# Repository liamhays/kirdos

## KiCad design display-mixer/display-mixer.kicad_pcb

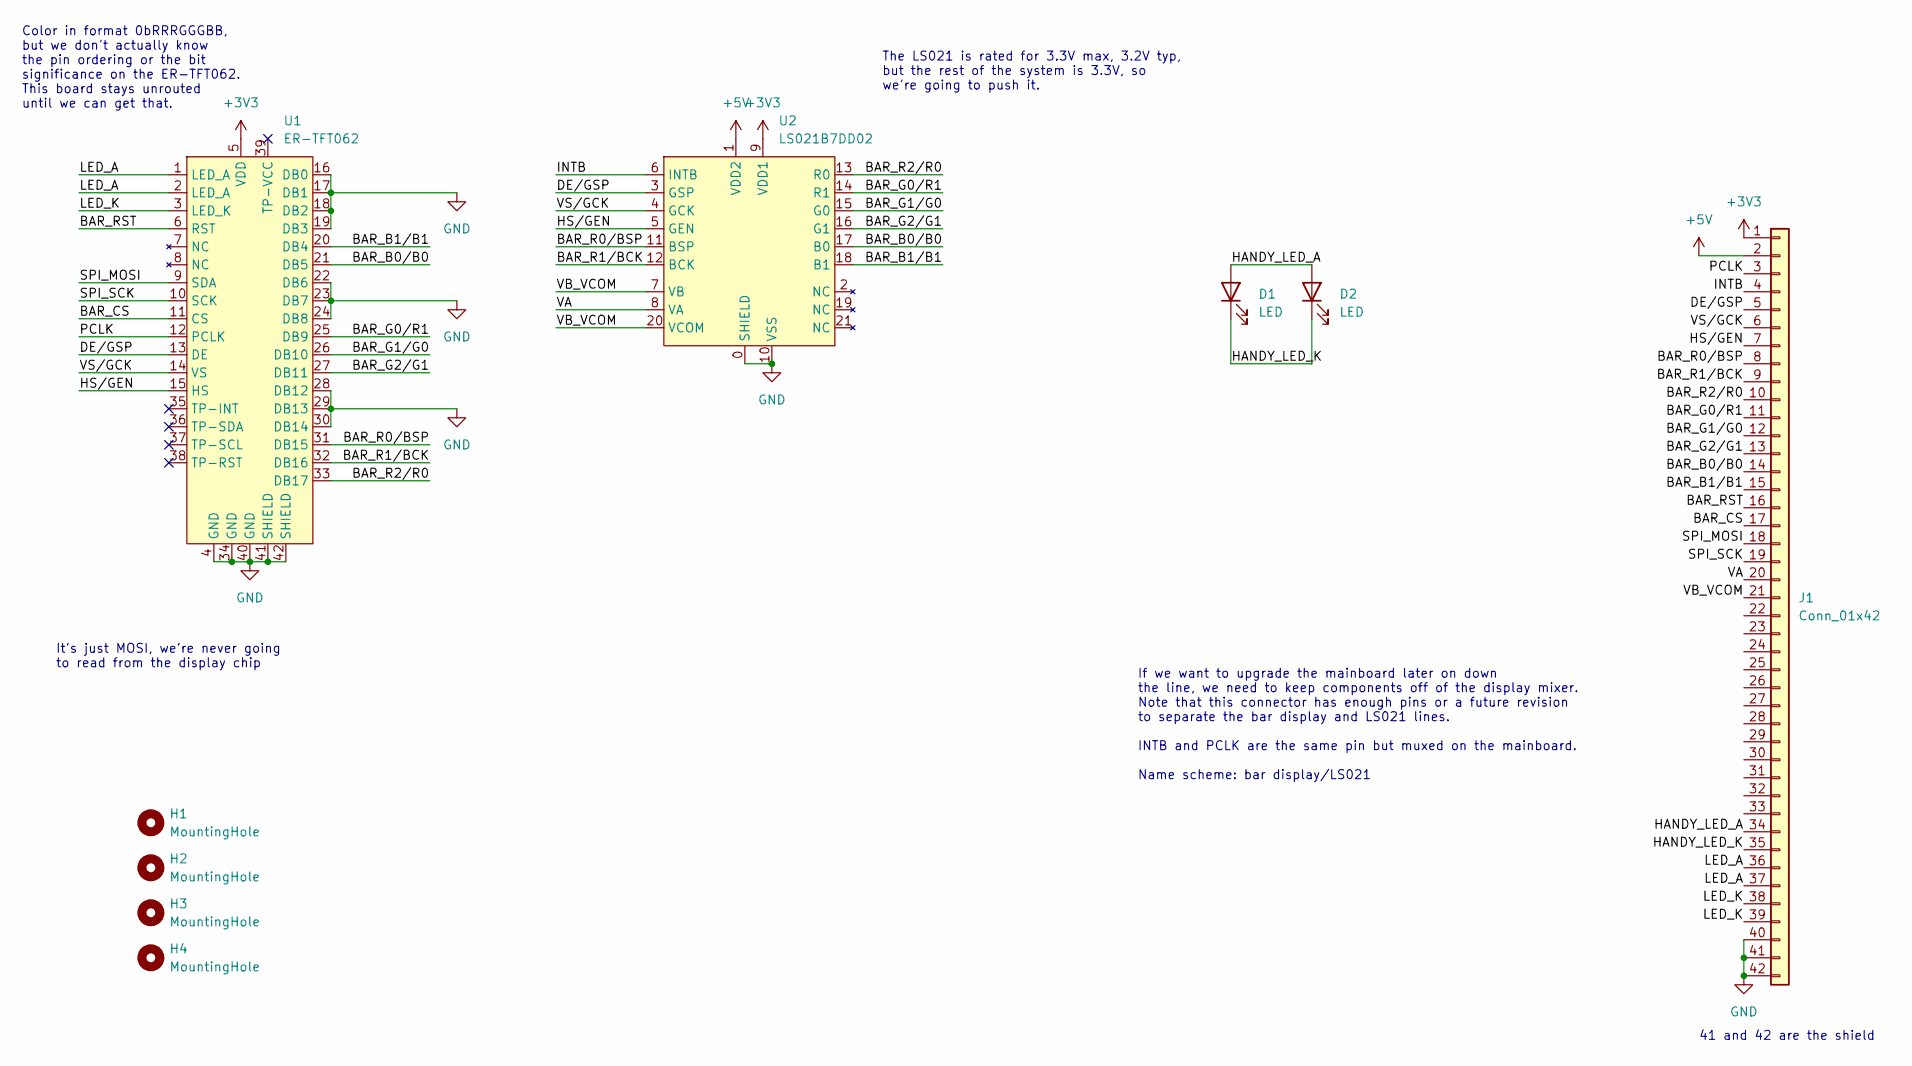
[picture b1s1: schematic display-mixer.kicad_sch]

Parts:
D1, D2: LED; LED_0603_1608Metric
H1, H2, H3, H4: MountingHole; MountingHole_3.2mm_M3
J1: Conn_01x42; JUSHUO_AFC07-S40FCC-00-FPC-SMD-0.5P
U1: ER-TFT062; JUSHUO_AFC07-S40ECA-00-FPC-SMD_P0.50-40P_LCS-SJ-H2.0; JLCPCB Part # C262648
U2: LS021B7DD02; LS021_CONN_FPC-SMD_21P-P0.30-503566-2102

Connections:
+3V3: J1.1, U1.5 (VDD), U2.9 (VDD1)
+5V: J1.2, U2.1 (VDD2)
/BAR_B0/B0: J1.14, U1.21 (DB5), U2.17 (B0)
/BAR_B1/B1: J1.15, U1.20 (DB4), U2.18 (B1)
/BAR_CS: J1.17, U1.11 (CS)
/BAR_G0/R1: J1.11, U1.25 (DB9), U2.14 (R1)
/BAR_G1/G0: J1.12, U1.26 (DB10), U2.15 (G0)
/BAR_G2/G1: J1.13, U1.27 (DB11), U2.16 (G1)
/BAR_R0/BSP: J1.8, U1.31 (DB15), U2.11 (BSP)
/BAR_R1/BCK: J1.9, U1.32 (DB16), U2.12 (BCK)
/BAR_R2/R0: J1.10, U1.33 (DB17), U2.13 (R0)
/BAR_RST: J1.16, U1.6 (RST)
/DE/GSP: J1.5, U1.13 (DE), U2.3 (GSP)
/HANDY_LED_A: D1.2 (A), D2.2 (A), J1.34
/HANDY_LED_K: D1.1 (K), D2.1 (K), J1.35
/HS/GEN: J1.7, U1.15 (HS), U2.5 (GEN)
/INTB: J1.4, U2.6 (INTB)
/LED_A: J1.36, J1.37, U1.1 (LED_A), U1.2 (LED_A)
/LED_K: J1.38, J1.39, U1.3 (LED_K)
/PCLK: J1.3, U1.12 (PCLK)
/SPI_MOSI: J1.18, U1.9 (SDA)
/SPI_SCK: J1.19, U1.10 (SCK)
/VA: J1.20, U2.8 (VA)
/VB_VCOM: J1.21, U2.7 (VB), U2.20 (VCOM)
/VS/GCK: J1.6, U1.14 (VS), U2.4 (GCK)
GND: J1.40, J1.41, J1.42, U1.4 (GND), U1.16 (DB0), U1.17 (DB1), U1.18 (DB2), U1.19 (DB3), U1.22 (DB6), U1.23 (DB7), U1.24 (DB8), U1.28 (DB12), U1.29 (DB13), U1.30 (DB14), U1.34 (GND), U1.40 (GND), U1.41 (SHIELD), U1.42 (SHIELD), U2.0 (SHIELD), U2.10 (VSS)

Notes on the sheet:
If we want to upgrade the mainboard later on down the line, we need to keep components off of the display mixer. Note that this connector has enough pins or a future revision to separate the bar display and LS021 lines. INTB and PCLK are the same pin but muxed on the mainboard. Name scheme: bar dis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
It's just MOSI, we're never going to read from the display chip
Color in format 0bRRRGGGBB, but we don't actually know the pin ordering or the bit significance on the ER-TFT062. This board stays unrouted until we can get that.
41 and 42 are the shield
The LS021 is rated for 3.3V max, 3.2V typ, but the rest of the system is 3.3V, so we're going to push it.

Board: 2 copper layers, 9 parts (2 on the bottom side), 26 nets, no tracks yet.

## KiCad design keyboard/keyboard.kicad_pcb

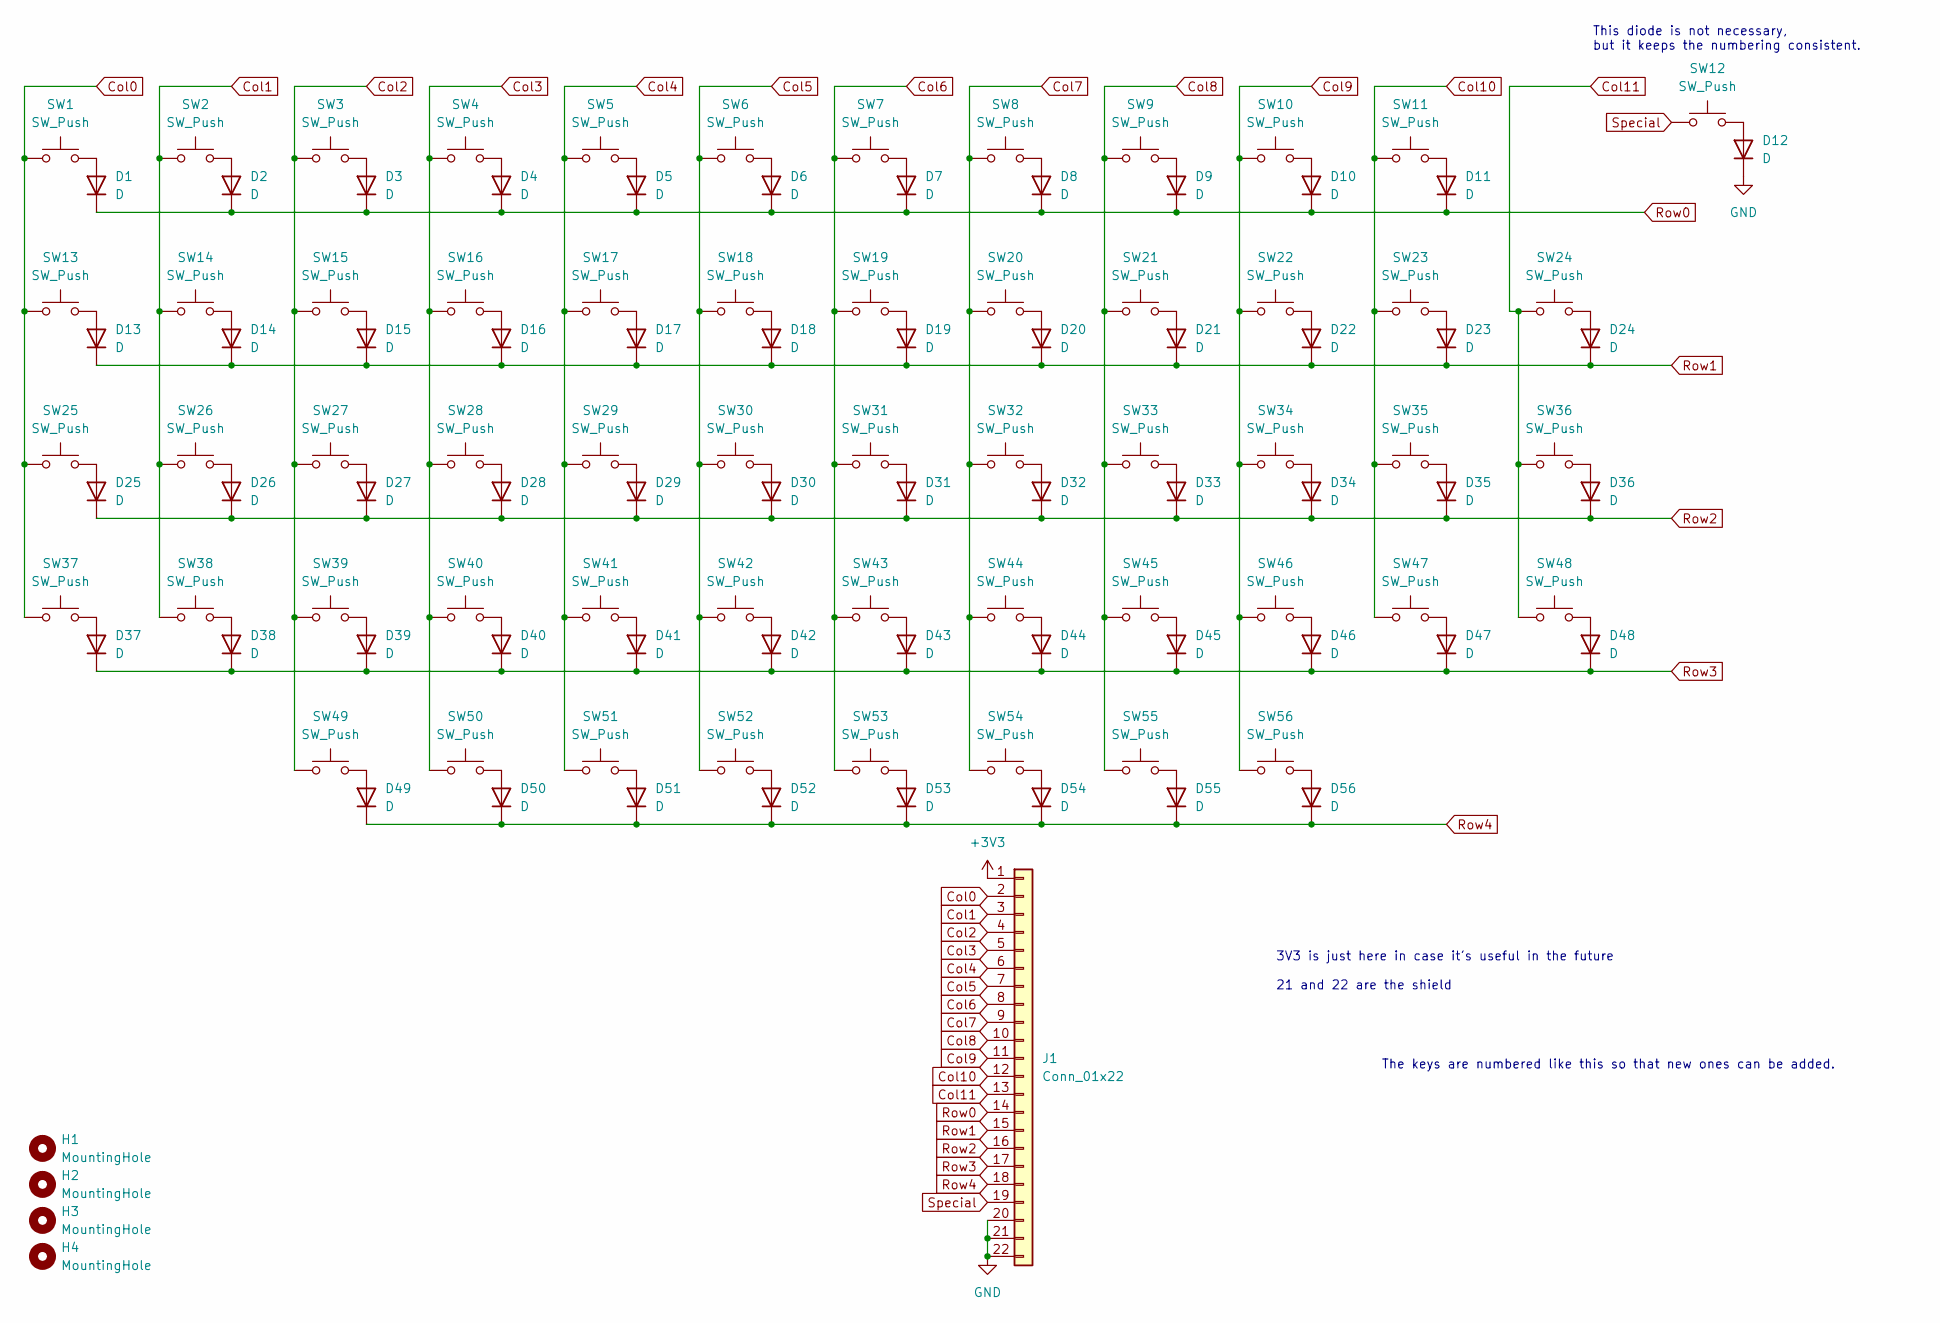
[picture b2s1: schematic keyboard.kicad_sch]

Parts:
D1, D2, D3, D4, D5, D6, D7, D8, D9, D10, D11, D12, D13, D14, D15, D16, D17, D18, D19, D20, D21, D22, D23, D24, D25, D26, D27, D28, D29, D30, D31, D32, D33, D34, D35, D36, D37, D38, D39, D40, D41, D42, D43, D44, D45, D46, D47, D48, D49, D50, D51, D52, D53, D54, D55, D56: D; D_0402_1005Metric
H1, H2, H3, H4: MountingHole; MountingHole_3.2mm_M3
J1: Conn_01x22; JUSHOU_AFC07-S20FCC-00-FPC-SMD_0.5P
SW1, SW2, SW3, SW4, SW5, SW6, SW7, SW8, SW9, SW10, SW11, SW12, SW13, SW14, SW15, SW16, SW17, SW18, SW19, SW20, SW21, SW22, SW23, SW24, SW25, SW26, SW27, SW28, SW29, SW30, SW31, SW32, SW33, SW34, SW35, SW36, SW37, SW38, SW39, SW40, SW41, SW42, SW43, SW44, SW45, SW46, SW47, SW48, SW49, SW50, SW51, SW52, SW53, SW54, SW55, SW56: SW_Push; SW_Kailh_Choc_V2

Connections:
+3V3: J1.1
Col0: J1.2, SW1.1, SW13.1, SW25.1, SW37.1
Col1: J1.3, SW2.1, SW14.1, SW26.1, SW38.1
Col2: J1.4, SW3.1, SW15.1, SW27.1, SW39.1, SW49.1
Col3: J1.5, SW4.1, SW16.1, SW28.1, SW40.1, SW50.1
Col4: J1.6, SW5.1, SW17.1, SW29.1, SW41.1, SW51.1
Col5: J1.7, SW6.1, SW18.1, SW30.1, SW42.1, SW52.1
Col6: J1.8, SW7.1, SW19.1, SW31.1, SW43.1, SW53.1
Col7: J1.9, SW8.1, SW20.1, SW32.1, SW44.1, SW54.1
Col8: J1.10, SW9.1, SW21.1, SW33.1, SW45.1, SW55.1
Col9: J1.11, SW10.1, SW22.1, SW34.1, SW46.1, SW56.1
Col10: J1.12, SW11.1, SW23.1, SW35.1, SW47.1
Col11: J1.13, SW24.1, SW36.1, SW48.1
GND: D12.1 (K), J1.20, J1.21, J1.22
unnamed: D1.2 (A), SW1.2
unnamed: D2.2 (A), SW2.2
unnamed: D3.2 (A), SW3.2
unnamed: D4.2 (A), SW4.2
unnamed: D5.2 (A), SW5.2
unnamed: D6.2 (A), SW6.2
unnamed: D7.2 (A), SW7.2
unnamed: D8.2 (A), SW8.2
unnamed: D9.2 (A), SW9.2
unnamed: D10.2 (A), SW10.2
unnamed: D11.2 (A), SW11.2
unnamed: D12.2 (A), SW12.2
unnamed: D13.2 (A), SW13.2
unnamed: D14.2 (A), SW14.2
unnamed: D15.2 (A), SW15.2
unnamed: D16.2 (A), SW16.2
unnamed: D17.2 (A), SW17.2
unnamed: D18.2 (A), SW18.2
unnamed: D19.2 (A), SW19.2
unnamed: D20.2 (A), SW20.2
unnamed: D21.2 (A), SW21.2
unnamed: D22.2 (A), SW22.2
unnamed: D23.2 (A), SW23.2
unnamed: D24.2 (A), SW24.2
unnamed: D25.2 (A), SW25.2
unnamed: D26.2 (A), SW26.2
unnamed: D27.2 (A), SW27.2
unnamed: D28.2 (A), SW28.2
unnamed: D29.2 (A), SW29.2
unnamed: D30.2 (A), SW30.2
unnamed: D31.2 (A), SW31.2
unnamed: D32.2 (A), SW32.2
unnamed: D33.2 (A), SW33.2
unnamed: D34.2 (A), SW34.2
unnamed: D35.2 (A), SW35.2
unnamed: D36.2 (A), SW36.2
unnamed: D37.2 (A), SW37.2
unnamed: D38.2 (A), SW38.2
unnamed: D39.2 (A), SW39.2
unnamed: D40.2 (A), SW40.2
unnamed: D41.2 (A), SW41.2
unnamed: D42.2 (A), SW42.2
unnamed: D43.2 (A), SW43.2
unnamed: D44.2 (A), SW44.2
unnamed: D45.2 (A), SW45.2
unnamed: D46.2 (A), SW46.2
unnamed: D47.2 (A), SW47.2
unnamed: D48.2 (A), SW48.2
unnamed: D49.2 (A), SW49.2
unnamed: D50.2 (A), SW50.2
unnamed: D51.2 (A), SW51.2
unnamed: D52.2 (A), SW52.2
unnamed: D53.2 (A), SW53.2
unnamed: D54.2 (A), SW54.2
unnamed: D55.2 (A), SW55.2
unnamed: D56.2 (A), SW56.2
Row0: D1.1 (K), D2.1 (K), D3.1 (K), D4.1 (K), D5.1 (K), D6.1 (K), D7.1 (K), D8.1 (K), D9.1 (K), D10.1 (K), D11.1 (K), J1.14
Row1: D13.1 (K), D14.1 (K), D15.1 (K), D16.1 (K), D17.1 (K), D18.1 (K), D19.1 (K), D20.1 (K), D21.1 (K), D22.1 (K), D23.1 (K), D24.1 (K), J1.15
Row2: D25.1 (K), D26.1 (K), D27.1 (K), D28.1 (K), D29.1 (K), D30.1 (K), D31.1 (K), D32.1 (K), D33.1 (K), D34.1 (K), D35.1 (K), D36.1 (K), J1.16
Row3: D37.1 (K), D38.1 (K), D39.1 (K), D40.1 (K), D41.1 (K), D42.1 (K), D43.1 (K), D44.1 (K), D45.1 (K), D46.1 (K), D47.1 (K), D48.1 (K), J1.17
Row4: D49.1 (K), D50.1 (K), D51.1 (K), D52.1 (K), D53.1 (K), D54.1 (K), D55.1 (K), D56.1 (K), J1.18
Special: J1.19, SW12.1

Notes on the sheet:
3V3 is just here in case it's useful in the future 21 and 22 are the shield
The keys are numbered like this so that new ones can be added.
This diode is not necessary, but it keeps the numbering consistent.

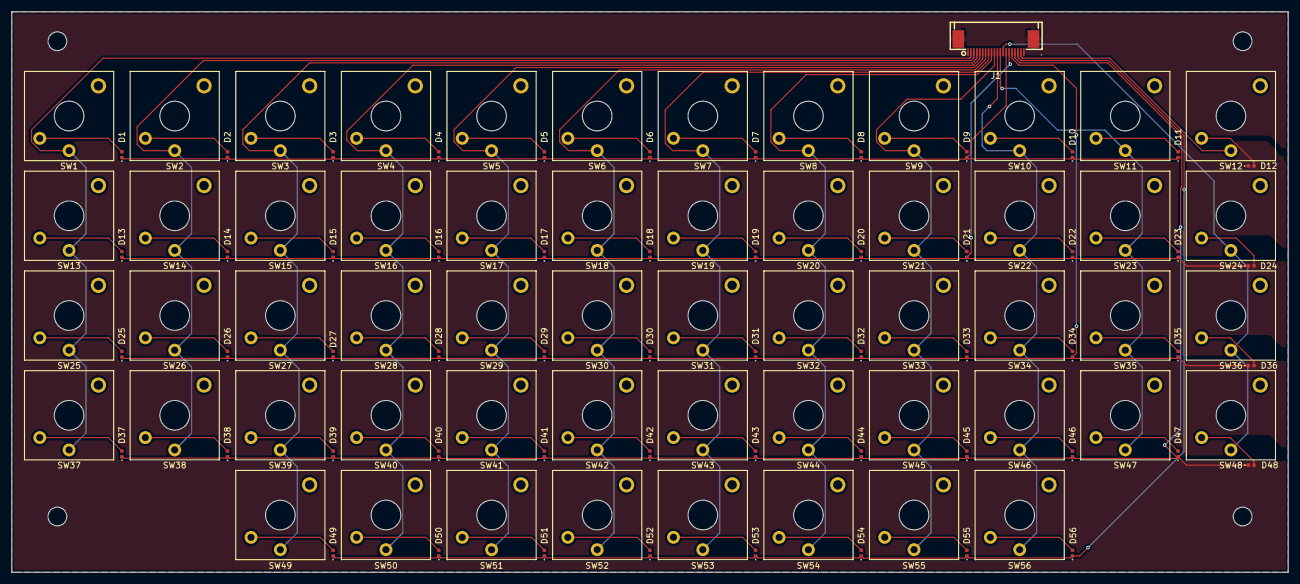
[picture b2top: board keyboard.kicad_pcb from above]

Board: 2 copper layers, 217.5 x 95.5 mm, 117 parts (0 on the bottom side), 75 nets.
